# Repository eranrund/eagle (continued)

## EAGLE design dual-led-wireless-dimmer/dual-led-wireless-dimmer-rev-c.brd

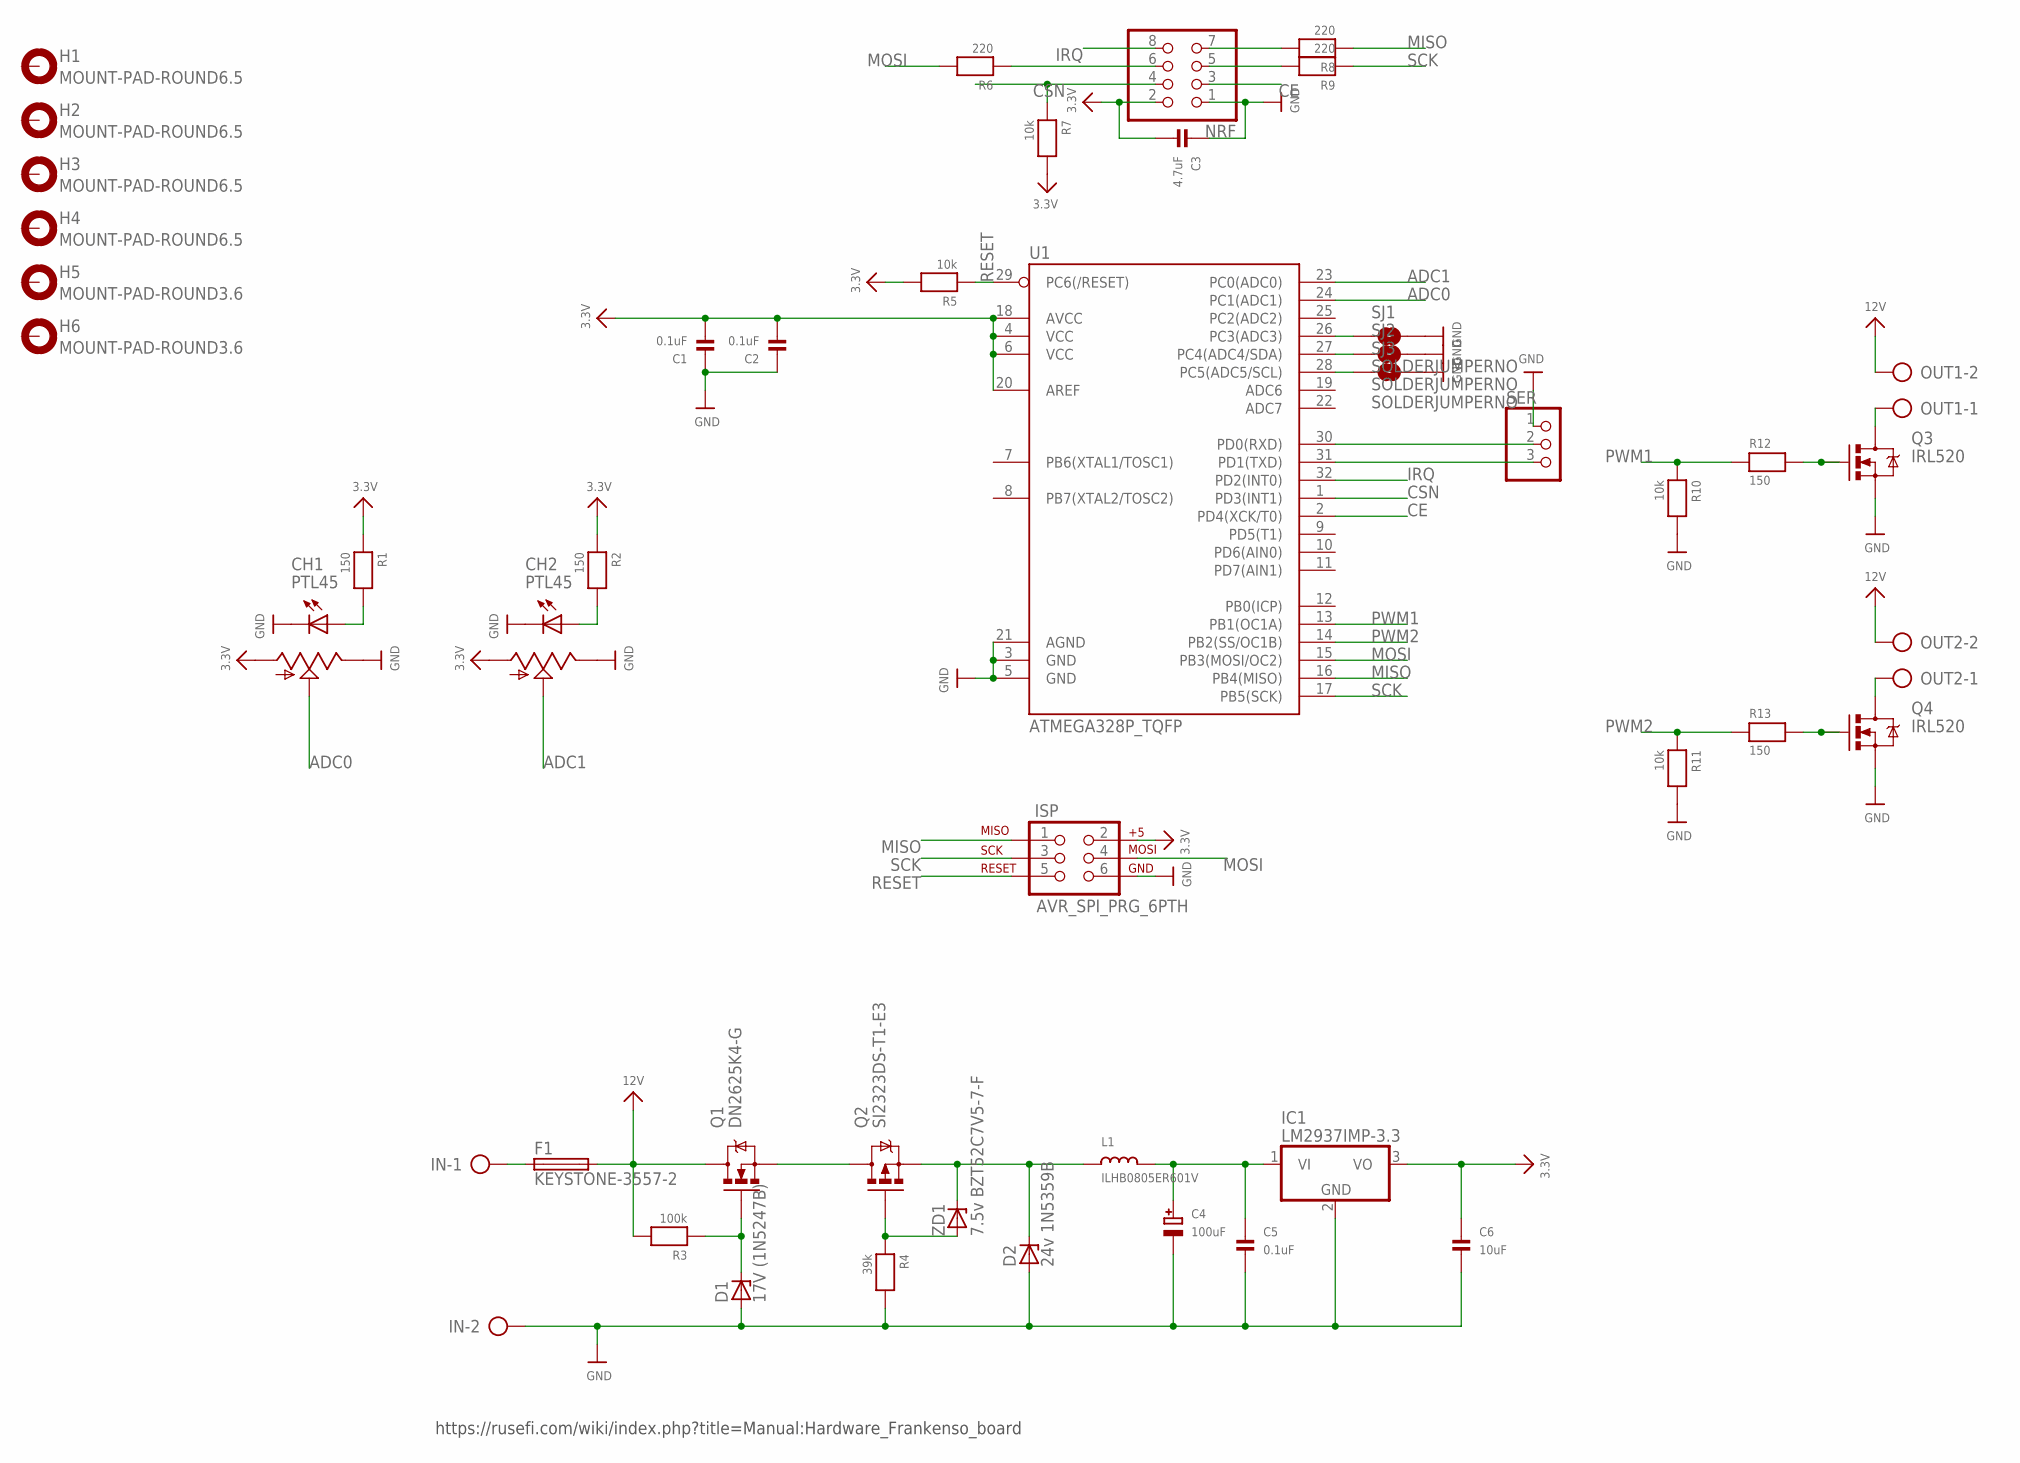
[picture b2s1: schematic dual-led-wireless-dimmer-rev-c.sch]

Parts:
C1, C2, C5: 0.1uF; 0805
C3: 4.7uF; 0805
C4: 100uF; PANASONIC_D
C6: 10uF; 0805
CH1, CH2: PTL45; BOURNS-PTL45
D1: 17V (1N5247B); ZDIO-5
D2: 24v 1N5359B; DO41Z10
F1: KEYSTONE-3557-2
H1, H2, H3, H4: MOUNT-PAD-ROUND6.5; 6,5-PAD
H5, H6: MOUNT-PAD-ROUND3.6; 3,6-PAD
IC1: LM2937IMP-3.3; TO263-3
IN: AK500/2-H
ISP: AVR_SPI_PRG_6PTH; 2X3
L1: ILHB0805ER601V; 0805
NRF: PINHD-2X4; 2X04
OUT1, OUT2: AK500/2-H
Q1: DN2625K4-G; DPAK
Q2: SI2323DS-T1-E3; SOT23-3
Q3, Q4: IRL520; TO220V
R1, R2, R12, R13: 150; 0805
R3: 100k; 0805
R4: 39k; 0805
R5, R7, R10, R11: 10k; 0805
R6, R8, R9: 220; 0805
SER: PINHD-1X3; 1X03
SJ1, SJ2, SJ3: SOLDERJUMPERNO; SJ_2S-NO
U1: ATMEGA328P_TQFP; TQFP32-08
ZD1: 7.5v BZT52C7V5-7-F; SOD123

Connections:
3.3V: C1.2, C2.2, C3.2, C6.1, CH1.1 (A), CH2.1 (A), IC1.3 (VO), ISP.2, NRF.2, R1.1, R2.1, R5.2, R7.2, U1.4 (VCC), U1.6 (VCC), U1.18 (AVCC), U1.20 (AREF)
12V: F1.R1 (2), F1.R2 (2), OUT1.2, OUT2.2, Q1.4 (D), R3.2
ADC0: CH1.2 (S), U1.24 (PC1(ADC1))
ADC1: CH2.2 (S), U1.23 (PC0(ADC0))
CE: NRF.3, U1.2 (PD4(XCK/T0))
CSN: NRF.4, R7.1, U1.1 (PD3(INT1))
GND: C1.1, C2.1, C3.1, C4.-, C5.2, C6.2, CH1.3 (E), CH1.E (LED-), CH2.3 (E), CH2.E (LED-), D1.A, D2.A, IC1.2 (GND), IN.2, ISP.6, NRF.1, Q3.3 (S), Q4.3 (S), R4.2, R10.2, R11.2, SER.1, SJ1.2, SJ2.2, SJ3.2, U1.3 (GND), U1.5 (GND), U1.21 (AGND)
IRQ: NRF.8, U1.32 (PD2(INT0))
MISO: ISP.1, R8.1, U1.16 (PB4(MISO))
MOSI: ISP.4, R6.2, U1.15 (PB3(MOSI/OC2))
unnamed: Q3.1 (G), R12.2
unnamed: Q4.1 (G), R13.2
unnamed: CH1.B (LED+), R1.2
unnamed: CH2.B (LED+), R2.2
unnamed: F1.L1 (1), F1.L2 (1), IN.1
unnamed: OUT1.1, Q3.2 (D)
unnamed: NRF.6, R6.1
unnamed: OUT2.1, Q4.2 (D)
unnamed: NRF.7, R8.2
unnamed: SJ1.1, U1.26 (PC3(ADC3))
unnamed: D1.C, Q1.1 (G), R3.1
unnamed: SJ2.1, U1.27 (PC4(ADC4/SDA))
unnamed: Q1.3 (S), Q2.3 (D)
unnamed: Q2.1 (G), R4.1, ZD1.A
unnamed: D2.C, L1.1, Q2.2 (S), ZD1.C
unnamed: SJ3.1, U1.28 (PC5(ADC5/SCL))
unnamed: C4.+, C5.1, IC1.1 (VI), L1.2
unnamed: SER.3, U1.31 (PD1(TXD))
unnamed: SER.2, U1.30 (PD0(RXD))
unnamed: NRF.5, R9.2
PWM1: R10.1, R12.1, U1.13 (PB1(OC1A))
PWM2: R11.1, R13.1, U1.14 (PB2(SS/OC1B))
RESET: ISP.5, R5.1, U1.29 (PC6(/RESET))
SCK: ISP.3, R9.1, U1.17 (PB5(SCK))

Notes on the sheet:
https://rusefi.com/wiki/index.php?title=Manual:Hardware_Frankenso_board

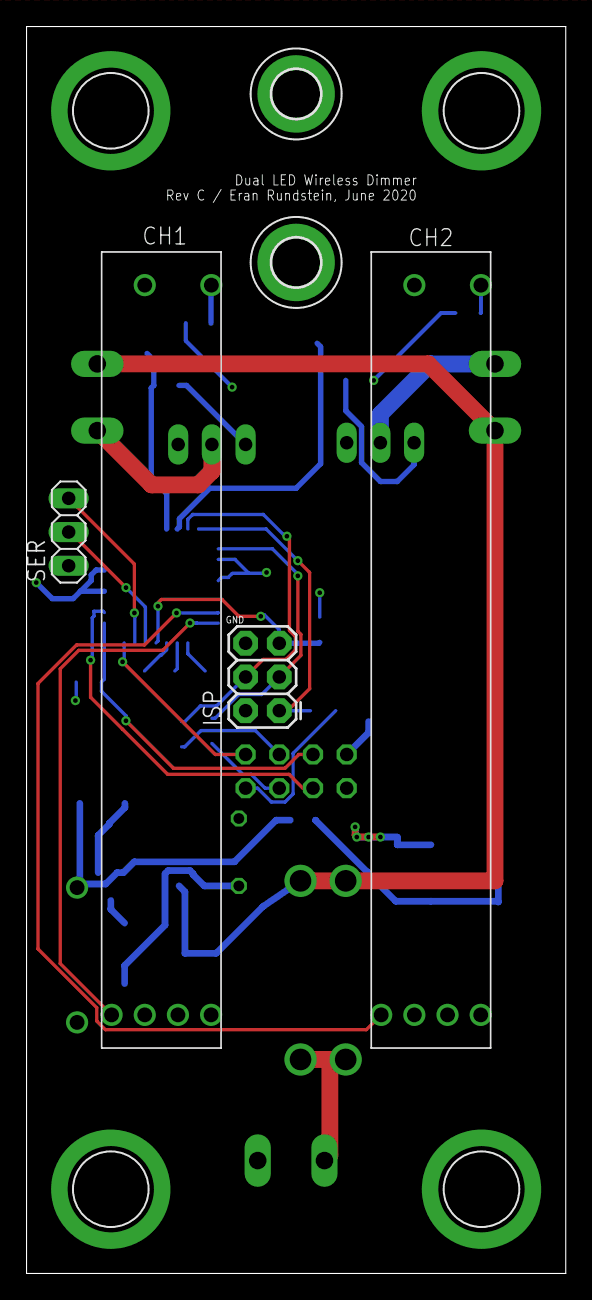
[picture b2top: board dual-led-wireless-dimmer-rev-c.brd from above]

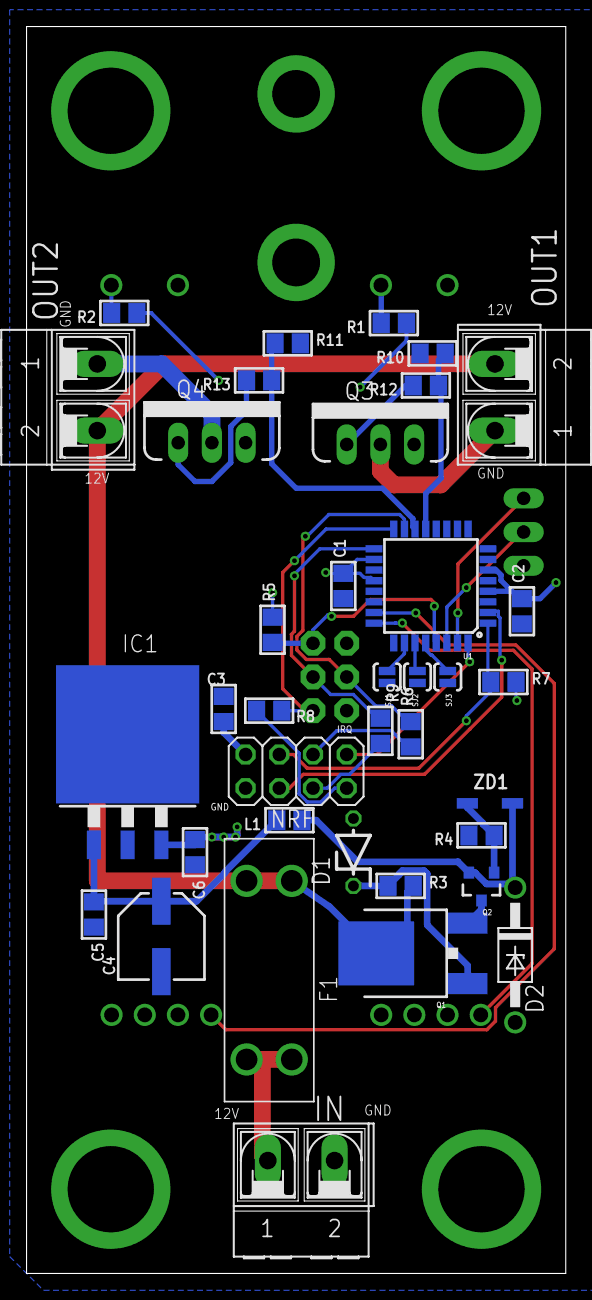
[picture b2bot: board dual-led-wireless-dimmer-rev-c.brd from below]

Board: 2 copper layers, 40.6 x 94.0 mm, 47 parts (37 on the bottom side), 34 nets.

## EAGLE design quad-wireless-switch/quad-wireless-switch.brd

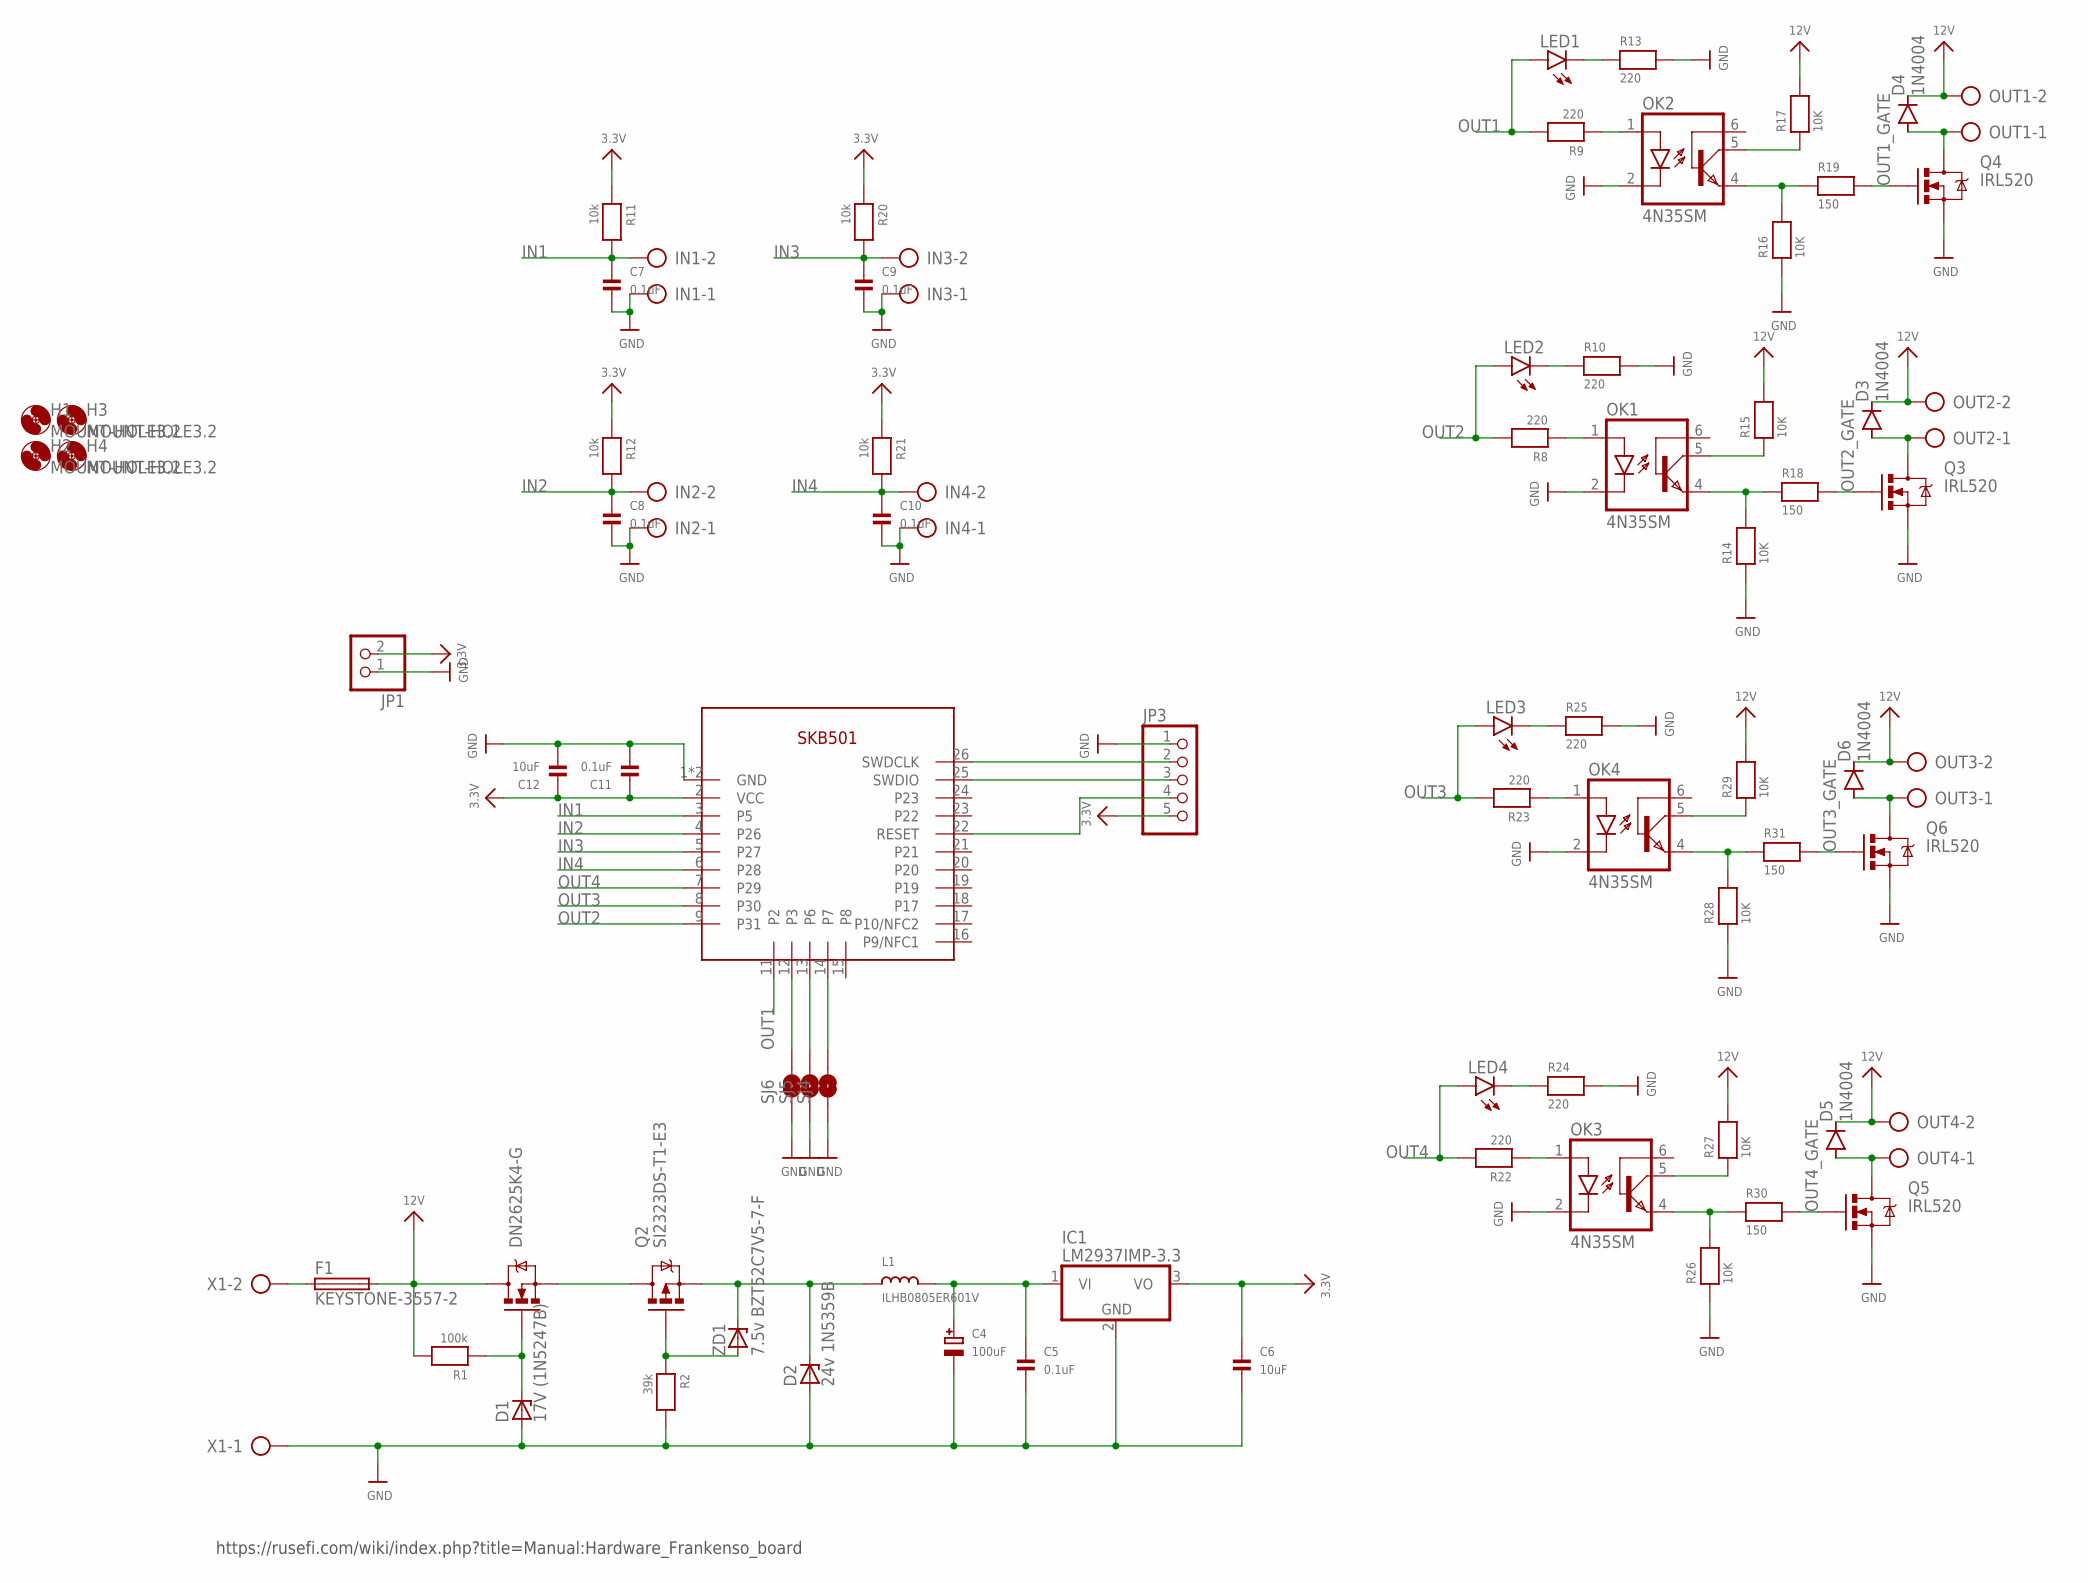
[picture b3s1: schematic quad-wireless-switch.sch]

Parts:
C4: 100uF; PANASONIC_D
C5, C7, C8, C9, C10, C11: 0.1uF; 0805
C6, C12: 10uF; 0805
D1: 17V (1N5247B); ZDIO-5
D2: 24v 1N5359B; DO41Z10
D3, D4, D5, D6: 1N4004; DO41-10
F1: KEYSTONE-3557-2
H1, H2, H3, H4: MOUNT-HOLE3.2; 3,2
IC1: LM2937IMP-3.3; TO263-3
IN1, IN2, IN3, IN4: AK500/2-H
JP1: PINHD-1X2; 1X02
JP3: PINHD-1X5; 1X05
L1: ILHB0805ER601V; 0805
LED1, LED2, LED3, LED4: LED5MM
OK1, OK2, OK3, OK4: 4N35SM; DIL6-SMD
OUT1, OUT2, OUT3, OUT4: AK500/2-H
Q1: DN2625K4-G; DPAK
Q2: SI2323DS-T1-E3; SOT23-3
Q3, Q4, Q5, Q6: IRL520; TO220V
R1: 100k; 0805
R2: 39k; 0805
R8, R9, R10, R13, R22, R23, R24, R25: 220; 0805
R11, R12, R20, R21: 10k; 0805
R14, R15, R16, R17, R26, R27, R28, R29: 10K; 0805
R18, R19, R30, R31: 150; 0805
SJ4, SJ5, SJ6: SOLDERJUMPERNO; SJ_2S-NO
U2: SDB501; SKB501
X1: AK500/2-H
ZD1: 7.5v BZT52C7V5-7-F; SOD123

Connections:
3.3V: C6.1, C11.1, C12.1, IC1.3 (VO), JP1.2, JP3.5, R11.1, R12.1, R20.1, R21.1, U2.2 (VCC)
12V: D3.C, D4.C, D5.C, D6.C, F1.R1 (2), F1.R2 (2), OUT1.2, OUT2.2, OUT3.2, OUT4.2, Q1.4 (D), R1.2, R15.2, R17.2, R27.2, R29.2
GND: C4.-, C5.2, C6.2, C7.2, C8.2, C9.2, C10.2, C11.2, C12.2, D1.A, D2.A, IC1.2 (GND), IN1.1, IN2.1, IN3.1, IN4.1, JP1.1, JP3.1, OK1.2 (C), OK2.2 (C), OK3.2 (C), OK4.2 (C), Q3.3 (S), Q4.3 (S), Q5.3 (S), Q6.3 (S), R2.2, R10.2, R13.2, R14.1, R16.1, R24.2, R25.2, R26.1, R28.1, SJ4.1, SJ5.1, SJ6.1, U2.1 (GND), U2.10 (GND), X1.1
IN1: C7.1, IN1.2, R11.2, U2.3 (P5)
IN2: C8.1, IN2.2, R12.2, U2.4 (P26)
IN3: C9.1, IN3.2, R20.2, U2.5 (P27)
IN4: C10.1, IN4.2, R21.2, U2.6 (P28)
unnamed: LED1.K (C), R13.1
unnamed: OK2.4 (EMI), R16.2, R19.1
unnamed: D3.A, OUT2.1, Q3.2 (D)
unnamed: LED2.K (C), R10.1
unnamed: F1.L1 (1), F1.L2 (1), X1.2
unnamed: D4.A, OUT1.1, Q4.2 (D)
unnamed: SJ4.2, U2.14 (P7)
unnamed: OK1.5 (COL), R15.1
unnamed: SJ5.2, U2.13 (P6)
unnamed: SJ6.2, U2.12 (P3)
unnamed: D1.C, Q1.1 (G), R1.1
unnamed: Q1.3 (S), Q2.3 (D)
unnamed: Q2.1 (G), R2.1, ZD1.A
unnamed: D2.C, L1.1, Q2.2 (S), ZD1.C
unnamed: C4.+, C5.1, IC1.1 (VI), L1.2
unnamed: OK1.1 (A), R8.1
unnamed: OK2.5 (COL), R17.1
unnamed: OK1.4 (EMI), R14.2, R18.1
unnamed: OK2.1 (A), R9.1
unnamed: D6.A, OUT3.1, Q6.2 (D)
unnamed: LED3.K (C), R25.1
unnamed: OK4.5 (COL), R29.1
unnamed: OK4.1 (A), R23.1
unnamed: OK4.4 (EMI), R28.2, R31.1
unnamed: D5.A, OUT4.1, Q5.2 (D)
unnamed: LED4.K (C), R24.1
unnamed: OK3.5 (COL), R27.1
unnamed: OK3.1 (A), R22.1
unnamed: OK3.4 (EMI), R26.2, R30.1
unnamed: JP3.2, U2.26 (SWDCLK)
unnamed: JP3.3, U2.25 (SWDIO)
unnamed: JP3.4, U2.22 (RESET)
OUT1: LED1.A, R9.2, U2.11 (P2)
OUT1_GATE: Q4.1 (G), R19.2
OUT2: LED2.A, R8.2, U2.9 (P31)
OUT2_GATE: Q3.1 (G), R18.2
OUT3: LED3.A, R23.2, U2.8 (P30)
OUT3_GATE: Q6.1 (G), R31.2
OUT4: LED4.A, R22.2, U2.7 (P29)
OUT4_GATE: Q5.1 (G), R30.2

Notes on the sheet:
https://rusefi.com/wiki/index.php?title=Manual:Hardware_Frankenso_board

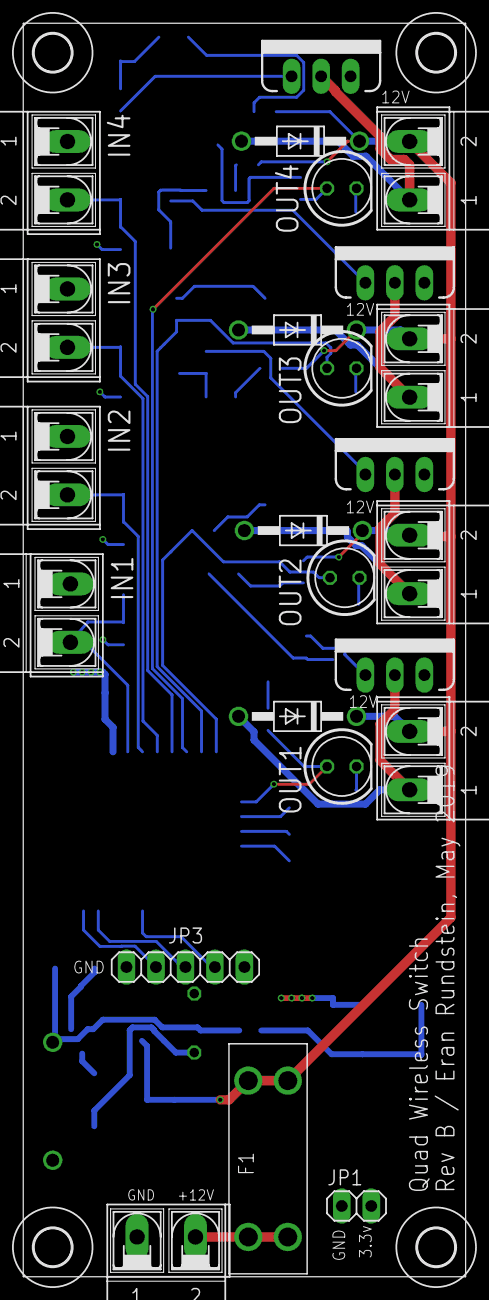
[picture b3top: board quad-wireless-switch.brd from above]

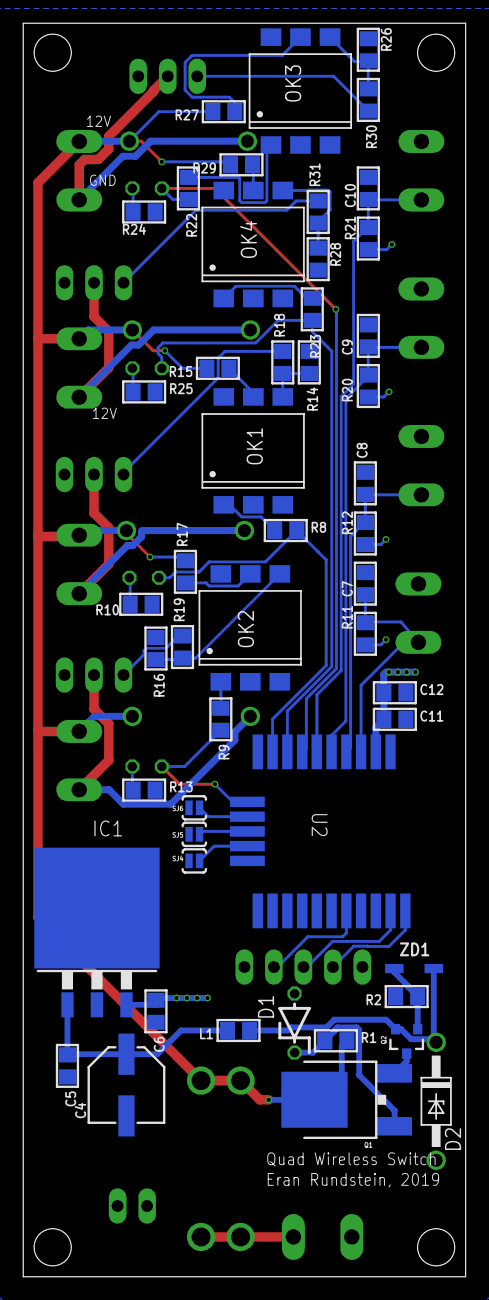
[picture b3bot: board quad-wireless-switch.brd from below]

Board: 2 copper layers, 38.1 x 108.0 mm, 78 parts (50 on the bottom side), 47 nets.

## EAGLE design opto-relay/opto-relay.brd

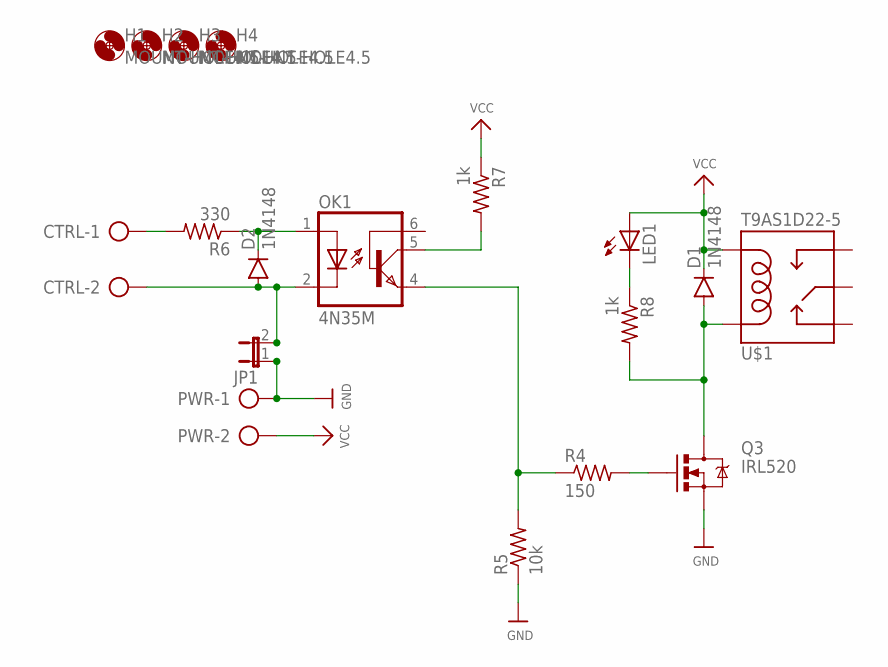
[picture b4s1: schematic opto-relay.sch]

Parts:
CTRL: AK500/2
D1, D2: 1N4148; DIODE-1N4148
H1, H2, H3, H4: MOUNT-HOLE4.5; 4,5
JP1: JP1E; JP1
LED1: LED5MM
OK1: 4N35M; DIL06
PWR: AK500/2
Q3: IRL520; TO220V
R4: 150; 0207/10
R5: 10k; 0207/10
R6: 330; 0207/10
R7, R8: 1k; 0207/10
U$1: T9AS1D22-5; RELAY-T9A-2

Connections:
CTRL: OK1.4 (EMI), R4.1, R5.2
GND: JP1.1, PWR.1, Q3.3 (S), R5.1
unnamed: Q3.1 (G), R4.2
unnamed: LED1.K (C), R8.1
unnamed: CTRL.1, R6.2
unnamed: CTRL.2, D2.A, JP1.2, OK1.2 (C)
unnamed: D2.C, OK1.1 (A), R6.1
unnamed: D1.A, Q3.2 (D), R8.2, U$1.COIL1
unnamed: OK1.5 (COL), R7.2
VCC: D1.C, LED1.A, PWR.2, R7.1, U$1.COIL2

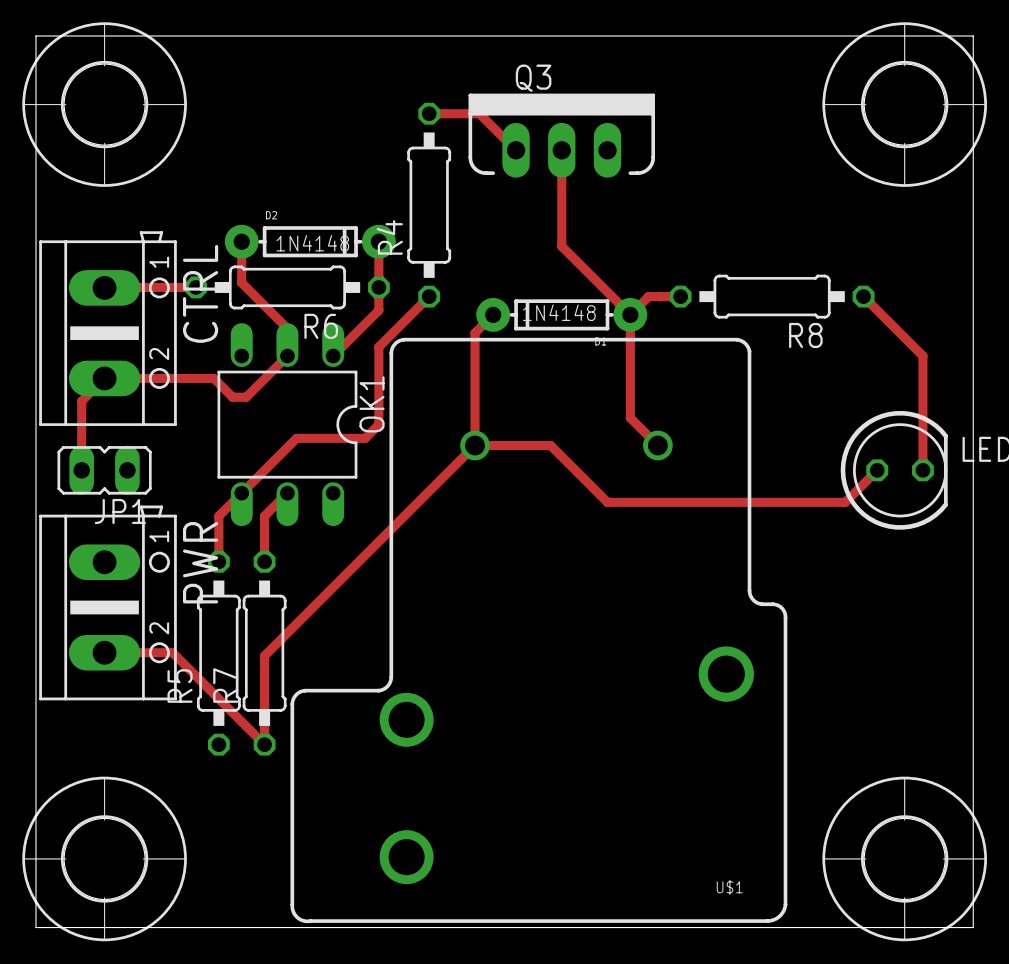
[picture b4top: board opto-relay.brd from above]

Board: 2 copper layers, 52.1 x 49.5 mm, 18 parts (0 on the bottom side), 10 nets.

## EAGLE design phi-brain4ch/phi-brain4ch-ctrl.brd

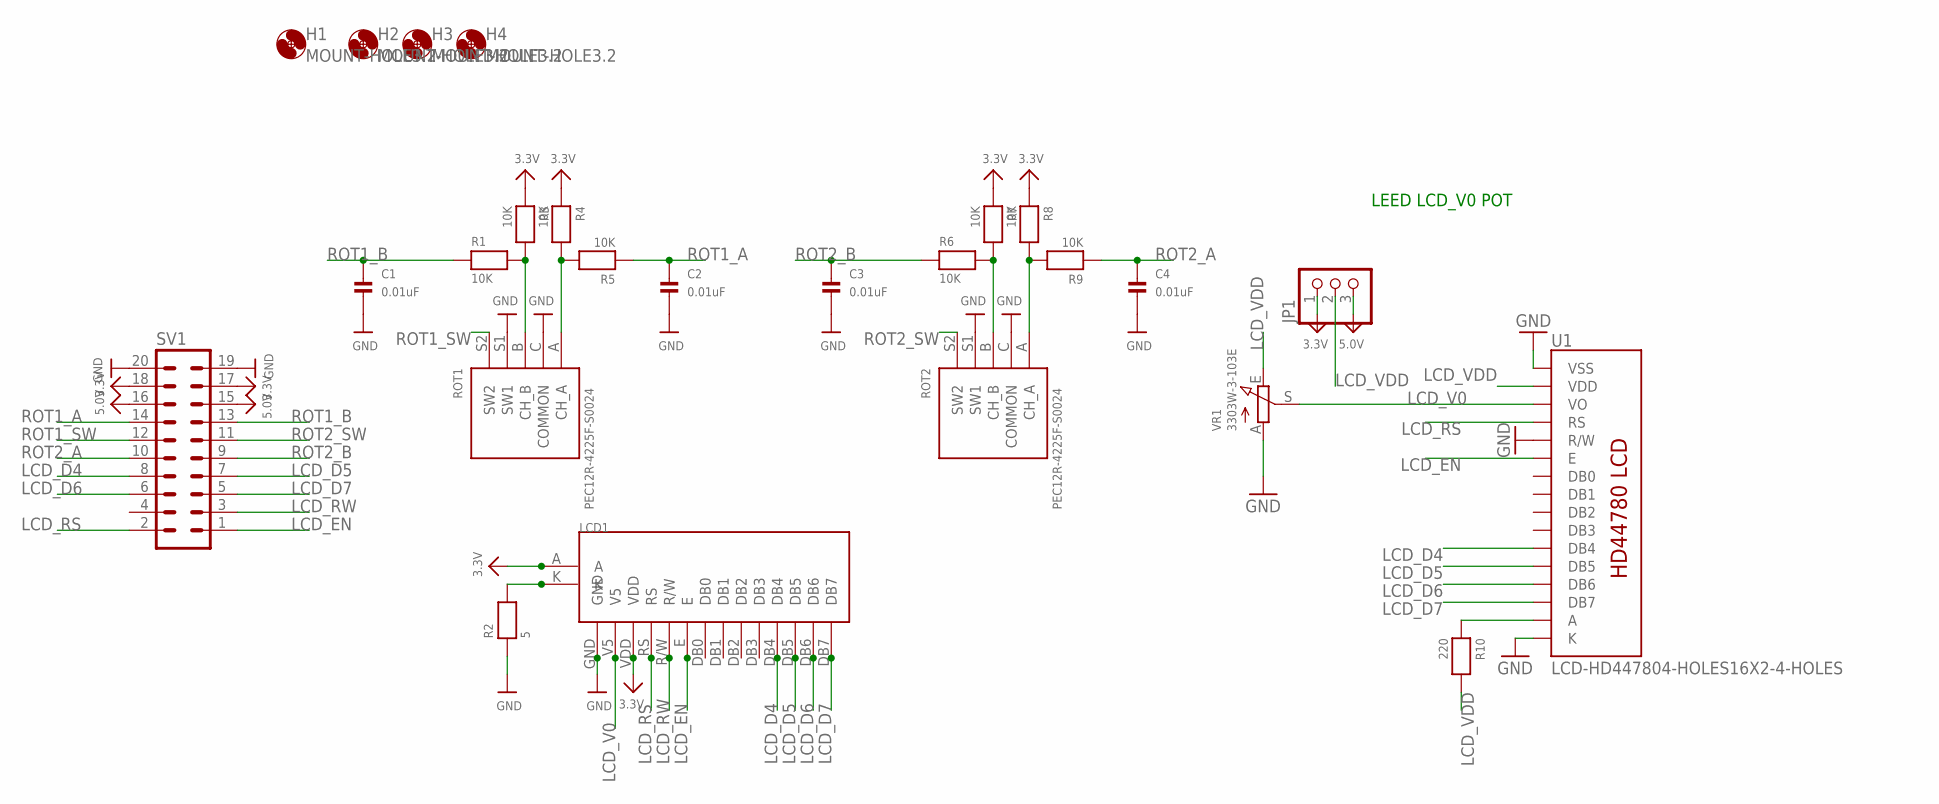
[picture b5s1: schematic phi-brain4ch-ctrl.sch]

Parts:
C1, C2, C3, C4: 0.01uF; 0805
H1, H2, H3, H4: MOUNT-HOLE3.2; 3,2
JP1: PINHD-1X3; 1X03
LCD1: NHD-C0220AA-FSW-FTW
R1, R3, R4, R5, R6, R7, R8, R9: 10K; _0805
R2: 5; _0805
R10: 220; _0805
ROT1, ROT2: PEC12R-4225F-S0024; PEC111-4XXXK-SXXXX
SV1: ML203MSMT; ML20SMT; PARTNO D2520-6V0C-AR-WE
U1: LCD-HD447804-HOLES16X2-4-HOLES; LCD-16X2-4HOLES
VR1: 3303W-3-103E; TRIMPOT_BOURNS3MM

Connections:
3.3V: JP1.1, LCD1.A, LCD1.VDD, R3.1, R4.1, R7.1, R8.1, SV1.17, SV1.18
5.0V: JP1.3, SV1.15, SV1.16
GND: C1.2, C2.2, C3.2, C4.2, LCD1.GND, R2.1, ROT1.C (COMMON), ROT1.S1 (SW1), ROT2.C (COMMON), ROT2.S1 (SW1), SV1.19, SV1.20, U1.1 (VSS), U1.5 (R/W), U1.16 (K), VR1.A
LCD_D4: LCD1.DB4, SV1.8, U1.11 (DB4)
LCD_D5: LCD1.DB5, SV1.7, U1.12 (DB5)
LCD_D6: LCD1.DB6, SV1.6, U1.13 (DB6)
LCD_D7: LCD1.DB7, SV1.5, U1.14 (DB7)
LCD_EN: LCD1.E, SV1.1, U1.6 (E)
LCD_RS: LCD1.RS, SV1.2, U1.4 (RS)
LCD_RW: LCD1.R/W, SV1.3
LCD_V0: LCD1.V5, U1.3 (VO), VR1.S
LCD_VDD: JP1.2, R10.2, U1.2 (VDD), VR1.E
unnamed: LCD1.K, R2.2
unnamed: R10.1, U1.15 (A)
unnamed: R6.2, R7.2, ROT2.B (CH_B)
unnamed: R8.2, R9.2, ROT2.A (CH_A)
unnamed: R1.2, R3.2, ROT1.B (CH_B)
unnamed: R4.2, R5.2, ROT1.A (CH_A)
ROT1_A: C2.1, R5.1, SV1.14
ROT1_B: C1.1, R1.1, SV1.13
ROT1_SW: ROT1.S2 (SW2), SV1.12
ROT2_A: C4.1, R9.1, SV1.10
ROT2_B: C3.1, R6.1, SV1.9
ROT2_SW: ROT2.S2 (SW2), SV1.11

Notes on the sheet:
LEED LCD_V0 POT

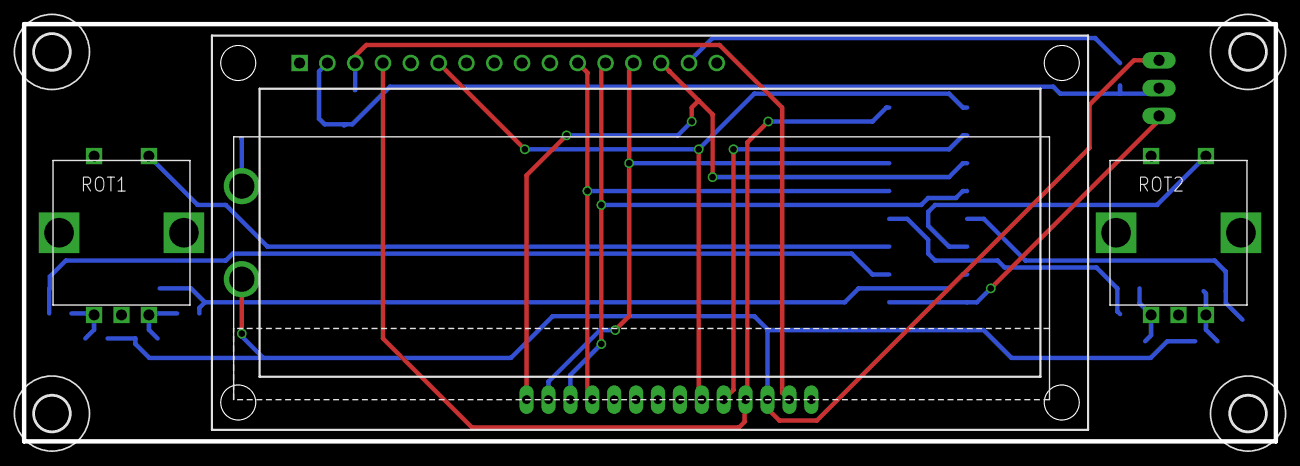
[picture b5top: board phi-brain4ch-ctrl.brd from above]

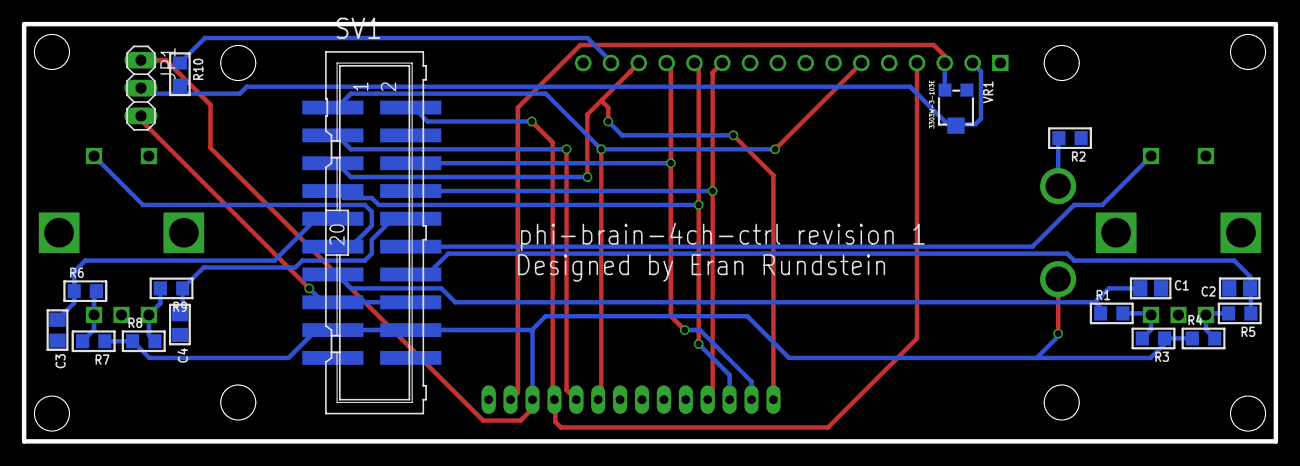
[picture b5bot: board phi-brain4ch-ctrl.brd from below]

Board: 2 copper layers, 114.3 x 38.1 mm, 25 parts (17 on the bottom side), 24 nets.

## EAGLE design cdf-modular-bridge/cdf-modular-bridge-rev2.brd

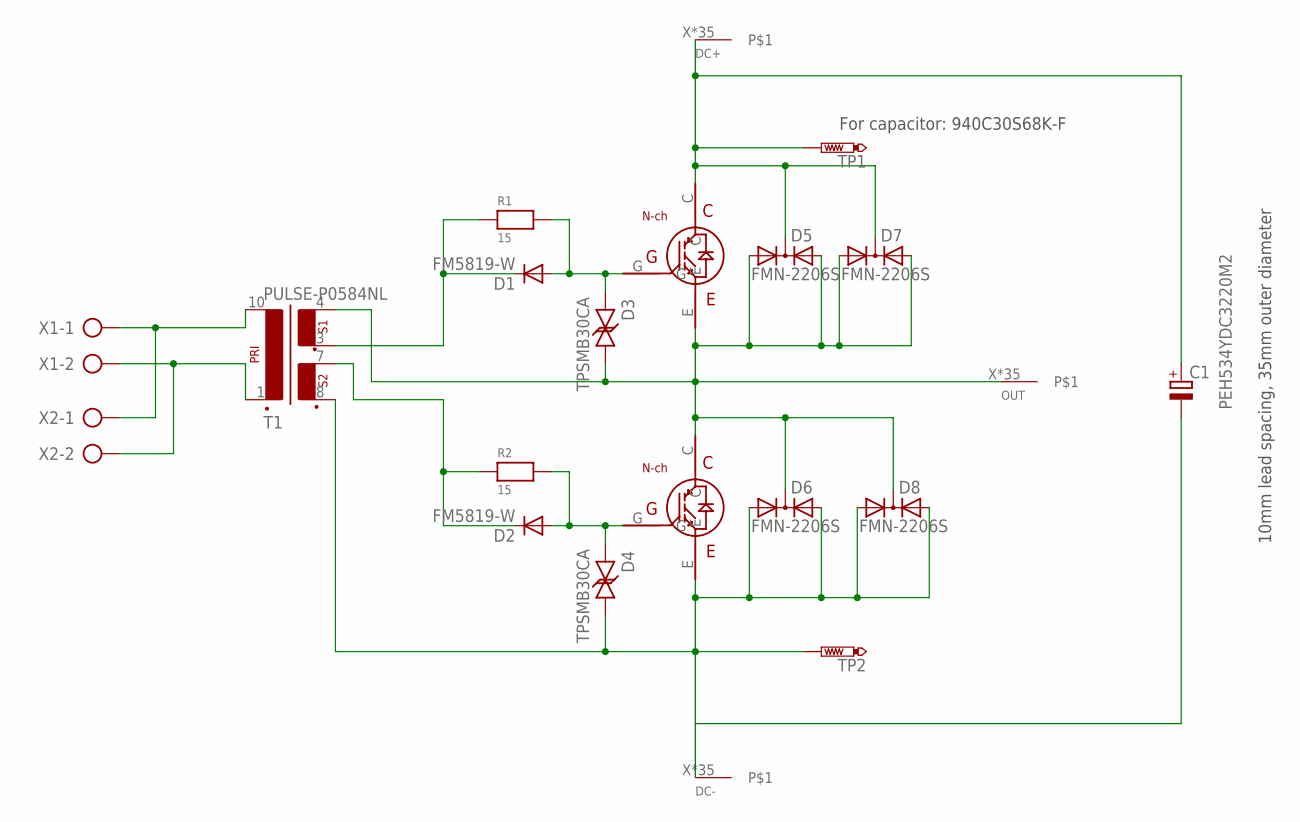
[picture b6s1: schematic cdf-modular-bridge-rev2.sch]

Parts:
C1: PEH534YDC3220M2; EB35D
D1, D2: FM5819-W; DO214AC
D3, D4: TPSMB30CA; TPSMB15CA
D5, D6, D7, D8: FMN-2206S; TO220ABS
DC+: BIG-ASS-HOLE
DC-: BIG-ASS-HOLE
OUT: BIG-ASS-HOLE
Q1, Q2: Ixgh48n60a3; IXGH40N60A
R1, R2: 15; 1206
T1: PULSE-P0584NL
TP1, TP2: PTR1PAD1-17; P1-17
X1, X2: AK500/2

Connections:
DC+: C1.+, D5.C, D7.C, DC+.X, DC+.X@1, DC+.X@2, DC+.X@3, DC+.X@4, DC+.X@5, DC+.X@6, DC+.X@7, DC+.X@8, DC+.X@9, DC+.X@10, DC+.X@11, DC+.X@12, DC+.X@13, DC+.X@14, DC+.X@15, DC+.X@16, DC+.X@17, DC+.X@18, DC+.X@19, DC+.X@20, DC+.X@21, DC+.X@22, DC+.X@23, DC+.X@24, DC+.X@25, DC+.X@26, DC+.X@27, DC+.X@28, DC+.X@29, DC+.X@30, DC+.X@31, DC+.X@32, DC+.X@34, DC+.X@120, Q1.C, TP1.TP
DC-: C1.-, D4.P$2, D6.A1, D6.A2, D8.A1, D8.A2, DC-.X, DC-.X@1, DC-.X@2, DC-.X@3, DC-.X@4, DC-.X@5, DC-.X@6, DC-.X@7, DC-.X@8, DC-.X@9, DC-.X@10, DC-.X@11, DC-.X@12, DC-.X@13, DC-.X@14, DC-.X@15, DC-.X@16, DC-.X@17, DC-.X@18, DC-.X@19, DC-.X@20, DC-.X@21, DC-.X@22, DC-.X@23, DC-.X@24, DC-.X@25, DC-.X@26, DC-.X@27, DC-.X@28, DC-.X@29, DC-.X@30, DC-.X@31, DC-.X@32, DC-.X@34, DC-.X@120, Q2.E, T1.8 (SEC2_POS), TP2.TP
unnamed: T1.10 (PRI_NEG), X1.1, X2.1
unnamed: T1.1 (PRI_POS), X1.2, X2.2
unnamed: D1.A, D3.P$1, Q1.G, R1.2
unnamed: D2.A, D4.P$1, Q2.G, R2.2
unnamed: D2.C, R2.1, T1.7 (SEC2_NEG)
unnamed: D1.C, R1.1, T1.3 (SEC1_POS)
OUT: D3.P$2, D5.A1, D5.A2, D6.C, D7.A1, D7.A2, D8.C, OUT.X, OUT.X@1, OUT.X@2, OUT.X@3, OUT.X@4, OUT.X@5, OUT.X@6, OUT.X@7, OUT.X@8, OUT.X@9, OUT.X@10, OUT.X@11, OUT.X@12, OUT.X@13, OUT.X@14, OUT.X@15, OUT.X@16, OUT.X@17, OUT.X@18, OUT.X@19, OUT.X@20, OUT.X@21, OUT.X@22, OUT.X@23, OUT.X@24, OUT.X@25, OUT.X@26, OUT.X@27, OUT.X@28, OUT.X@29, OUT.X@30, OUT.X@31, OUT.X@32, OUT.X@34, OUT.X@120, Q1.E, Q2.C, T1.4 (SEC1_NEG)

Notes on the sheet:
For capacitor: 940C30S68K-F
10mm lead spacing, 35mm outer diameter

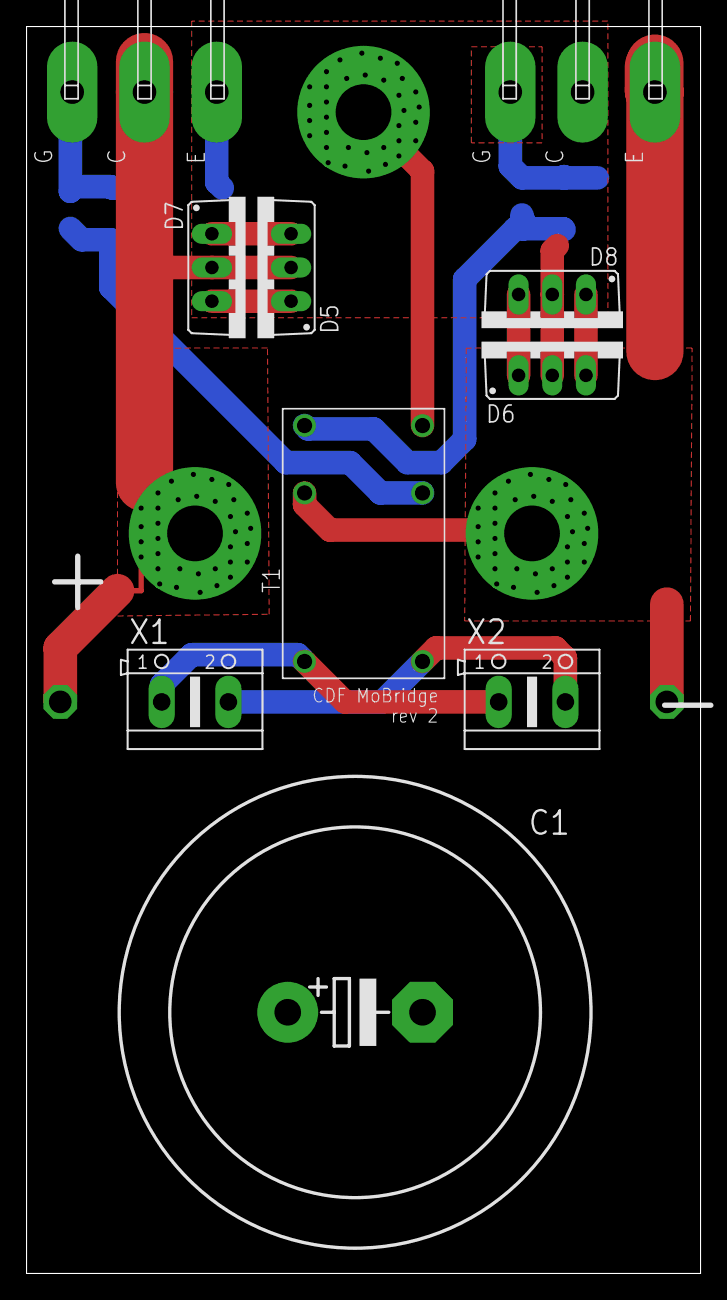
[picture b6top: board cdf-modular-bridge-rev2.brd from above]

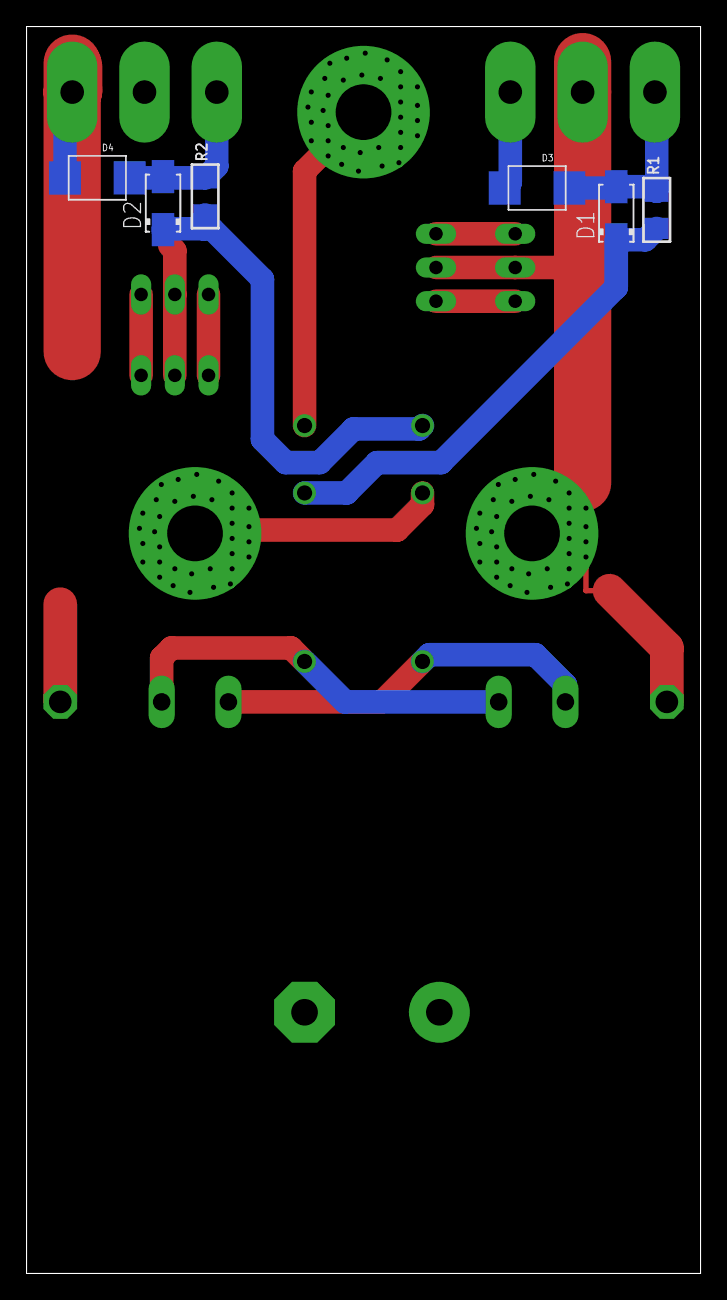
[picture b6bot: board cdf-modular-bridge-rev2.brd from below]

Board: 2 copper layers, 50.8 x 94.0 mm, 21 parts (6 on the bottom side), 9 nets.
